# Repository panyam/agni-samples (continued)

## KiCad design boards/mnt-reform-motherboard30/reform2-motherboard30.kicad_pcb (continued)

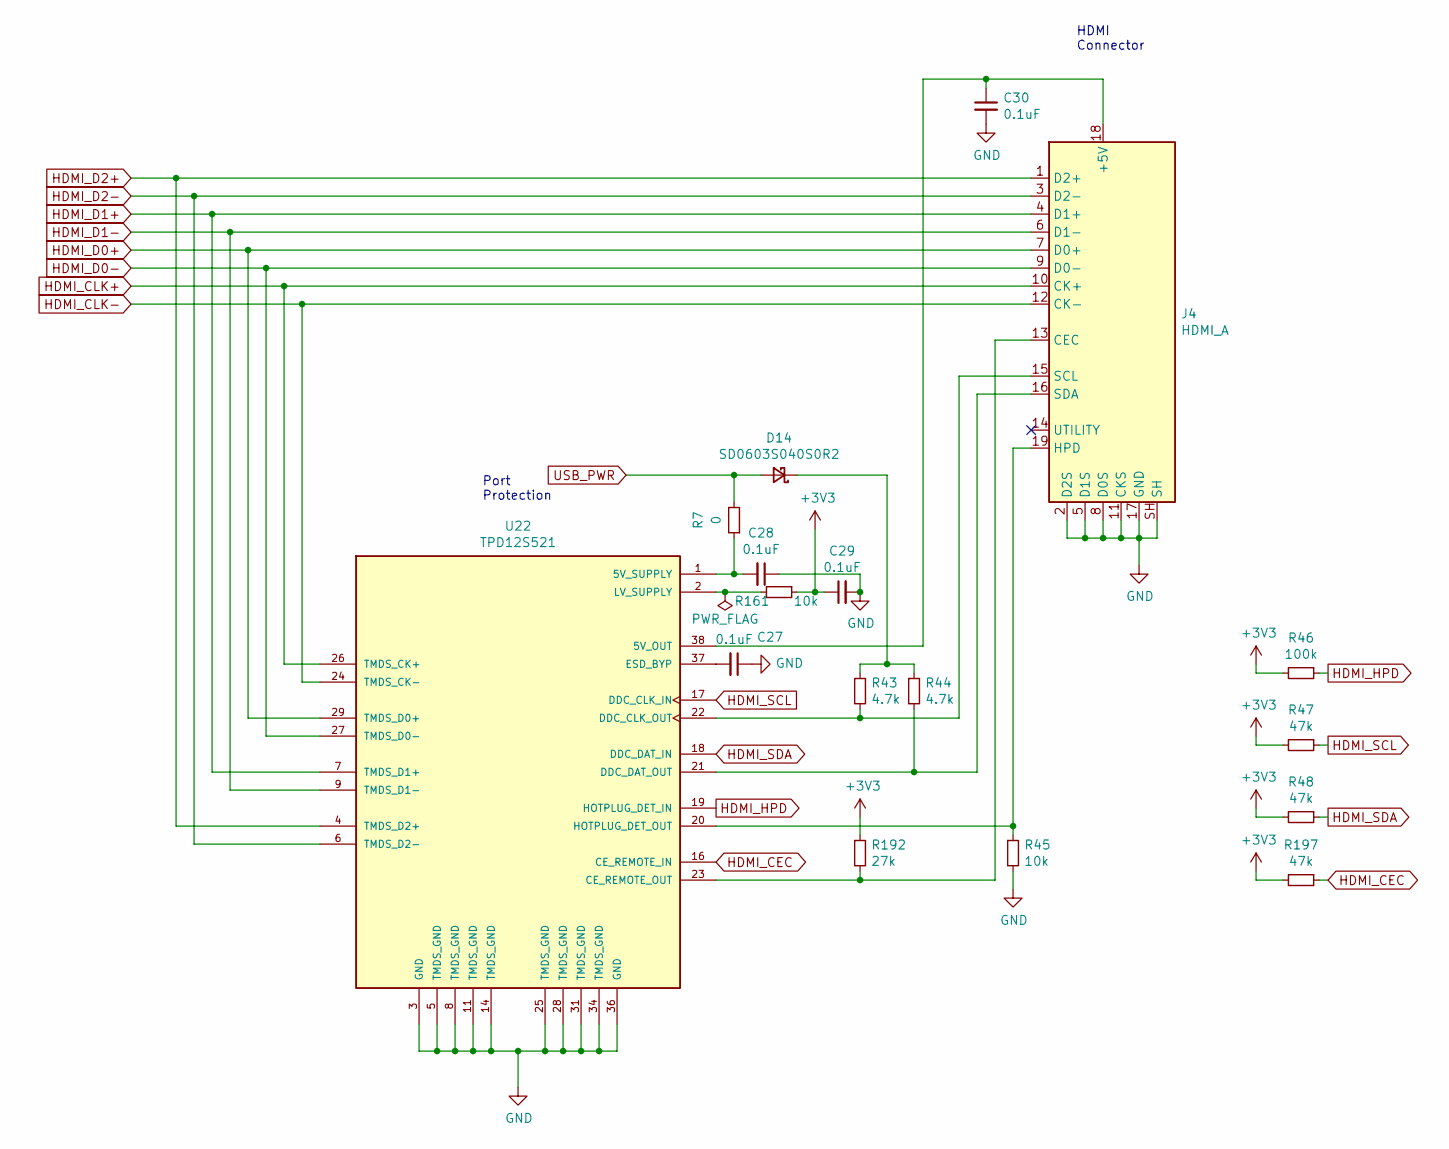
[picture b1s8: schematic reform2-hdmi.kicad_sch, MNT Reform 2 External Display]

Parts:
C27, C28, C29, C30: 0.1uF; C_0603_1608Metric
D14: SD0603S040S0R2; D_0603_1608Metric
J4: HDMI_A; HDMI-685119134923
R7: 0; R_0603_1608Metric
R43, R44: 4.7k; R_0603_1608Metric
R45, R161: 10k; R_0603_1608Metric
R46: 100k; R_0603_1608Metric
R47, R48, R197: 47k; R_0603_1608Metric
R192: 27k; R_0603_1608Metric
U22: TPD12S521; TSSOP50P640X120-38N

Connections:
+3V3: C29.1, R46.2, R47.2, R48.2, R161.1, R192.1, R197.2; also elsewhere on the board
GND: C27.1, C28.1, C29.2, C30.2, J4.2 (D2S), J4.5 (D1S), J4.8 (D0S), J4.11 (CKS), J4.17 (GND), J4.SH, R45.2, U22.3 (GND), U22.5 (TMDS_GND), U22.8 (TMDS_GND), U22.11 (TMDS_GND), U22.14 (TMDS_GND), U22.25 (TMDS_GND), U22.28 (TMDS_GND), U22.31 (TMDS_GND), U22.34 (TMDS_GND), U22.36 (GND); also elsewhere on the board
HDMI_CEC: R197.1, U22.16 (CE_REMOTE_IN); also elsewhere on the board
HDMI_CLK+: J4.10 (CK+), U22.13 (TMDS_CK+), U22.26 (TMDS_CK+); also elsewhere on the board
HDMI_CLK-: J4.12 (CK-), U22.15 (TMDS_CK-), U22.24 (TMDS_CK-); also elsewhere on the board
HDMI_D0+: J4.7 (D0+), U22.10 (TMDS_D0+), U22.29 (TMDS_D0+); also elsewhere on the board
HDMI_D0-: J4.9 (D0-), U22.12 (TMDS_D0-), U22.27 (TMDS_D0-); also elsewhere on the board
HDMI_D1+: J4.4 (D1+), U22.7 (TMDS_D1+), U22.32 (TMDS_D1+); also elsewhere on the board
HDMI_D1-: J4.6 (D1-), U22.9 (TMDS_D1-), U22.30 (TMDS_D1-); also elsewhere on the board
HDMI_D2+: J4.1 (D2+), U22.4 (TMDS_D2+), U22.35 (TMDS_D2+); also elsewhere on the board
HDMI_D2-: J4.3 (D2-), U22.6 (TMDS_D2-), U22.33 (TMDS_D2-); also elsewhere on the board
HDMI_HPD: R46.1, U22.19 (HOTPLUG_DET_IN); also elsewhere on the board
HDMI_SCL: R47.1, U22.17 (DDC_CLK_IN); also elsewhere on the board
HDMI_SDA: R48.1, U22.18 (DDC_DAT_IN); also elsewhere on the board
unnamed: D14.1 (K), R43.1, R44.1
unnamed: C30.1, J4.18 (+5V), U22.38 (5V_OUT)
unnamed: J4.13 (CEC), R192.2, U22.23 (CE_REMOTE_OUT)
unnamed: J4.19 (HPD), R45.1, U22.20 (HOTPLUG_DET_OUT)
unnamed: J4.15 (SCL), R43.2, U22.22 (DDC_CLK_OUT)
unnamed: J4.16 (SDA), R44.2, U22.21 (DDC_DAT_OUT)
unnamed: C28.2, R7.1, U22.1 (5V_SUPPLY)
unnamed: C27.2, U22.37 (ESD_BYP)
unnamed: R161.2, U22.2 (LV_SUPPLY)
USB_PWR: D14.2 (A), R7.2; also elsewhere on the board

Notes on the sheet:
HDMI Connector
Port Protection

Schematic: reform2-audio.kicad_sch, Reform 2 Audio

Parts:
C127, C147: 220uF; C_1210_3225Metric
C139, C151, C170: 4.7uF; C_0603_1608Metric
C141, C162, C163: 1uF; C_0603_1608Metric
C142, C143, C144, C154, C156, C158, C165, C166: 0.1uF; C_0603_1608Metric
C150: 10uF; C_0603_1608Metric
C157, C159: 470nF; C_0603_1608Metric
D10: SP0503BAHT; SOT-143
FB10, FB11, FB16, FB17, FB18, FB19, FB20, FB21: 100@100MHz 3A; L_0603_1608Metric
J7: SJ-43516-SMT
J16: LINE_IN; PinHeader_1x03_P2.00mm_Vertical
J21: Conn_01x04; JST_PH_B4B-PH-K_1x04_P2.00mm_Vertical
L8, L9, L10, L11: 15uH; L_1210_3225Metric
R66, R112: 220; R_0603_1608Metric
R114, R121, R138, R139, R150, R151: 33; R_0603_1608Metric
R135, R136: 4.7k; R_0603_1608Metric
R140: 680; R_0603_1608Metric
R141, R152: 0; R_0603_1608Metric
R142, R143: 47k; R_0603_1608Metric
R144: 220k; R_0603_1608Metric
U3: WM8960; QFN-32-1EP_5x5mm_P0.5mm_EP3.45x3.45mm_ThermalVias

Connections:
+3V3: FB18.1, FB20.1, FB21.1, R135.1, R136.1; also elsewhere on the board
+5V: R152.1; also elsewhere on the board
DAC_BCLK: R114.1; also elsewhere on the board
DAC_DIN: R150.1; also elsewhere on the board
DAC_DOUT: R121.1; also elsewhere on the board
DAC_MCLK: R138.2; also elsewhere on the board
DAC_RXFS: R139.1; also elsewhere on the board
DAC_SCL: R66.1; also elsewhere on the board
DAC_SDA: R112.1; also elsewhere on the board
DAC_TXFS: R151.1; also elsewhere on the board
GND: C139.2, C142.2, C143.2, C144.1, C150.2, C151.2, C154.2, C156.2, C158.2, C165.2, C166.2, C170.2, D10.1 (A), J7.4 (RING2), J16.1, R142.2, R143.2, U3.9 (DGND), U3.20 (SPKGND2), U3.24 (SPKGND1), U3.28 (AGND), U3.33 (GND); also elsewhere on the board
unnamed: FB10.2, L8.1
unnamed: FB11.2, L9.1
unnamed: FB16.2, L10.1
unnamed: FB17.2, L11.1
unnamed: C147.1, D10.4 (K), J7.3 (RING1), R143.1
unnamed: J7.6 (RING_SWITCH), R141.1, R144.2
unnamed: C141.1, D10.2 (K), J7.1 (SLEEVE), R140.2
unnamed: C127.1, D10.3 (K), J7.2 (TIP), R142.1
unnamed: C163.2, J16.2
unnamed: C162.2, J16.3
unnamed: C159.2, C166.1, J21.1, L11.2
unnamed: C159.1, C165.1, J21.2, L10.2
unnamed: C157.2, C158.1, J21.3, L9.2
unnamed: C156.1, C157.1, J21.4, L8.2
unnamed: R150.2, U3.16 (ADCDAT)
unnamed: R139.2, U3.15 (ADCLRC)
unnamed: C142.1, FB21.2, U3.32 (AVDD)
unnamed: R114.2, U3.12 (BCLK)
unnamed: R121.2, U3.14 (DACDAT)
unnamed: R151.2, U3.13 (DACLRC)
unnamed: C143.1, FB20.2, R144.1, U3.10 (DBVDD)
unnamed: C144.2, FB18.2, U3.8 (DCVDD)
unnamed: C127.2, U3.31 (HP_L)
unnamed: C147.2, U3.29 (HP_R)
unnamed: C141.2, U3.4 (LINPUT1)
unnamed: C162.1, U3.3 (LINPUT2)
unnamed: R141.2, U3.2 (LINPUT3)
unnamed: R138.1, U3.11 (MCLK)
unnamed: C170.1, R140.1, U3.1 (MICBIAS)
unnamed: C163.1, U3.6 (RINPUT2)
unnamed: R66.2, R135.2, U3.17 (SCLK)
unnamed: R112.2, R136.2, U3.18 (SDIN)
unnamed: C139.1, C151.1, FB19.2, U3.21 (SPKVDD2), U3.26 (SPKVDD1)
unnamed: FB11.1, U3.23 (SPK_LN)
unnamed: FB10.1, U3.25 (SPK_LP)
unnamed: FB17.1, U3.19 (SPK_RN)
unnamed: FB16.1, U3.22 (SPK_RP)
unnamed: C150.1, C154.1, U3.27 (VMID)
SPK_PWR: FB19.1, R152.2

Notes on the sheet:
value changed in 3.0, thanks chartreuse
CTIA standard TRRS
butterworth filter with 40khz cutoff: speaker ohms = 8 L = 22.5uH C = 0.35uF
Jack Detect
Audio Codec
Speakers: PUI AS01808AO-3-R 8 Ohm 1 W
NOTE: DCVDD could be 1.8v
more bass!
800mA

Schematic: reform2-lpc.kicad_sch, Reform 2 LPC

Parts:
BT1: CR1220; BatteryHolder_Keystone_3000_1x12mm
C7, C49, C50, C140: 0.1uF; C_0603_1608Metric
C46, C47: 10uF; C_0603_1608Metric
C48, C51: 18pF; C_0603_1608Metric; LCSC C107040
J8: USB_C_Receptacle_USB2.0; USB_C_Receptacle_HRO_TYPE-C-31-M-12; LCSC C165948
J18: QWIIC_LPC; JST_SH_SM04B-SRSS-TB_1x04-1MP_P1.00mm_Horizontal
J22: LPC_IO; PinHeader_2x08_P2.54mm_Vertical
J23: KDBSYSCTL; JST_PH_B4B-PH-K_1x04_P2.00mm_Vertical
R41: 0.02; R_0612_1632Metric
R68, R69: 4.7k; R_0603_1608Metric
R70, R72: 33; R_0603_1608Metric
R71, R195: 1.5k; R_0603_1608Metric
R73, R74, R75, R76, R124, R125, R126, R137, R157, R194: 0; R_0603_1608Metric
R128: 10k; R_0603_1608Metric
SW1: SW_DIP_x01; SW_DIP_SPSTx01_Slide_Omron_A6S-110x_W8.9mm_P2.54mm
SW2: SW_Push; UK-B0206-G3.8-250-JZ
TP4: LPCUSB_VBUS; TestPoint_Pad_D1.0mm; not fitted
U5: PCF8523T; SOIC-8_3.9x4.9mm_P1.27mm
U6: INA233; VSSOP-10_3x3mm_P0.5mm
U18: LPC11U24FBD48-301; LQFP-48_7x7mm_P0.5mm
Y2: 12MHz; Crystal_SMD_Abracon_ABM8G-4Pin_3.2x2.5mm
Y4: 32.768 kHz; Crystal_SMD_3215-2Pin_3.2x1.5mm

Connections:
1V2_PWR_EN: U18.2 (PIO1_19); also elsewhere on the board
3V3_PWR_EN: U18.48 (PIO1_16); also elsewhere on the board
5V_PWR_EN: U18.43 (PIO1_15); also elsewhere on the board
/Reform 2 Power/Reform 2 LPC/LPCUD_N: R72.2, U18.19 (USB_DM)
/Reform 2 Power/Reform 2 LPC/LPCUD_P: R70.2, U18.20 (USB_DP)
/Reform 2 Power/Reform 2 LPC/LPCUSB_VBUS: J8.A4 (VBUS), J8.A9 (VBUS), J8.B4 (VBUS), J8.B9 (VBUS), TP4.1
/Reform 2 Power/Reform 2 LPC/LPC_AD5: J22.7, U18.40 (PIO0_16)
/Reform 2 Power/Reform 2 LPC/LPC_AD7: J22.10, U18.42 (PIO0_23)
/Reform 2 Power/Reform 2 LPC/LPC_MISO0: R124.1, U18.27 (PIO0_8)
/Reform 2 Power/Reform 2 LPC/LPC_MISO1a: J22.2, U18.30 (PIO0_22)
/Reform 2 Power/Reform 2 LPC/LPC_MISO1b: R74.2, U18.26 (PIO1_21)
/Reform 2 Power/Reform 2 LPC/LPC_MOSI0: R125.1, U18.28 (PIO0_9)
/Reform 2 Power/Reform 2 LPC/LPC_MOSI1a: J22.14, U18.17 (PIO0_21)
/Reform 2 Power/Reform 2 LPC/LPC_MOSI1b: R75.2, U18.38 (PIO1_22)
/Reform 2 Power/Reform 2 LPC/LPC_RXDc: J23.3, U18.11 (PIO1_26)
/Reform 2 Power/Reform 2 LPC/LPC_SCK0a: R126.1, U18.29 (PIO0_10)
/Reform 2 Power/Reform 2 LPC/LPC_SCK0b: J22.1, U18.31 (PIO1_29)
/Reform 2 Power/Reform 2 LPC/LPC_SCK1b: R73.2, U18.13 (PIO1_20)
/Reform 2 Power/Reform 2 LPC/LPC_SCLKa: J22.9, U18.45 (PIO0_17)
/Reform 2 Power/Reform 2 LPC/LPC_SCLKc: R194.2, U18.24 (PIO1_28)
/Reform 2 Power/Reform 2 LPC/LPC_SSEL0: R157.1, U18.10 (PIO0_2)
/Reform 2 Power/Reform 2 LPC/LPC_SSEL1: R76.2, U18.18 (PIO1_23)
/Reform 2 Power/Reform 2 LPC/LPC_SWDIO: J22.8, U18.39 (PIO0_15)
/Reform 2 Power/Reform 2 LPC/LPC_TDI: J22.4, U18.32 (PIO0_11)
/Reform 2 Power/Reform 2 LPC/LPC_TDO: J22.6, U18.34 (PIO0_13)
/Reform 2 Power/Reform 2 LPC/LPC_TMS: J22.3, U18.33 (PIO0_12)
/Reform 2 Power/Reform 2 LPC/LPC_TXDc: J23.2, U18.12 (PIO1_27)
/Reform 2 Power/Reform 2 LPC/LPC_UFTOGG: SW1.2, U18.4 (PIO0_1)
/Reform 2 Power/Reform 2 LPC/LPC_UVBUS: R195.2, U18.14 (PIO0_3)
/Reform 2 Power/Reform 2 LPC/LPC_~TRST: J22.5, U18.35 (PIO0_14)
/Reform 2 Power/Reform 2 LPC/LPC_~USBCON: J22.13, U18.22 (PIO0_6)
AUX_PWR_EN: U18.23 (PIO0_7)
BAT1FUSED: R41.1, U6.10 (Vin+); also elsewhere on the board
BMON_CS: R76.1; also elsewhere on the board
BMON_SCK: R73.1; also elsewhere on the board
BMON_SDI: R75.1; also elsewhere on the board
BMON_SDO: R74.1, R128.1; also elsewhere on the board
CHGBAT: R41.2, U6.8 (Vbus), U6.9 (Vin-); also elsewhere on the board
CHG_RNG: U18.1 (PIO1_25); also elsewhere on the board
DAC_SCL: U5.6 (SCL); also elsewhere on the board
DAC_SDA: U5.5 (SDA); also elsewhere on the board
GND: BT1.2 (-), C7.2, C46.2, C47.2, C48.2, C49.2, C50.2, C51.2, C140.1, J8.A1 (GND), J8.A12 (GND), J8.B1 (GND), J8.B12 (GND), J8.S1 (SHIELD), J18.1, J22.16, J23.4, SW1.1, SW2.1, U5.4 (VSS), U6.1 (A1), U6.2 (A0), U6.7 (GND), U18.5 (VSS), U18.41 (VSS), Y2.2, Y2.4; also elsewhere on the board
IMX_RESETn: R194.1; also elsewhere on the board
IMX_RTC_IRQ: R137.1; also elsewhere on the board
IMX_WAKE: U18.21 (PIO1_24); also elsewhere on the board
INA_SCL: J18.4, R69.2, U6.5 (SCL), U18.15 (PIO0_4); also elsewhere on the board
INA_SDA: J18.3, R68.2, U6.4 (SDA), U18.16 (PIO0_5); also elsewhere on the board
LPC_MISO: R124.2; also elsewhere on the board
LPC_MOSI: R125.2; also elsewhere on the board
LPC_RXDa: J22.12, U18.46 (PIO0_18); also elsewhere on the board
LPC_SCK: R126.2; also elsewhere on the board
LPC_SS0: R157.2; also elsewhere on the board
LPC_TXDa: J22.11, U18.47 (PIO0_19); also elsewhere on the board
LPC_UART2_RX: U18.37 (PIO1_14); also elsewhere on the board
LPC_UART2_TX: U18.36 (PIO1_13); also elsewhere on the board
LPC_VCC: C7.1, C46.1, C47.1, C49.1, C50.1, C140.2, J18.2, J22.15, J23.1, R68.1, R69.1, R71.1, R128.2, R195.1, U5.8 (VDD), U6.6 (VS), U18.8 (VDD), U18.44 (VDD); also elsewhere on the board
LPC_~RESET: SW2.2, U18.3 (PIO0_0)
unnamed: BT1.1 (+), U5.3 (VBAT)
unnamed: J8.A6 (D+), J8.B6 (D+), R70.1, R71.2
unnamed: J8.A7 (D-), J8.B7 (D-), R72.1
unnamed: U5.1 (OSCI), Y4.1
unnamed: U5.2 (OSCO), Y4.2
unnamed: R137.2, U5.7 (~INT1/CLKOUT)
unnamed: C51.1, U18.6 (XTALIN), Y2.3
unnamed: C48.1, U18.7 (XTALOUT), Y2.1
PCIE1_PWR_EN: U18.9 (PIO0_20); also elsewhere on the board
USB_PWR_EN: U18.25 (PIO1_31)

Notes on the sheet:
LPC Flashing Port
no longer used
System Controller
Expansion Port
I2C lines pulled up by SYS 3v3 power near DAC
Power Switches
Keyboard System Control Port (SYSCTL)
Powered by coin cell when batteries removed
Powered by main batteries in standby
LPC Qwiic I2C Interface
I2C ADDR 1000_000
Voltage / Current Monitor
Realtime Clock

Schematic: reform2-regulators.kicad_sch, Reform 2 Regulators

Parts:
C3: 0.33uF; C_0603_1608Metric
C16, C19, C148, C172: 10uF; C_0805_2012Metric
C17, C18, C149, C171: 470nF; C_0603_1608Metric; LCSC C1589
C33, C35, C167, C188: 4.7uF; C_0603_1608Metric
C34, C37: 10uF; C_0603_1608Metric
C36, C38: 6.8pF; C_0603_1608Metric
C82: 2.2uF; C_0603_1608Metric
C93, C94, C95, C96, C97, C173, C174, C175, C176, C177: 22uF; C_0603_1608Metric; LCSC C140782
C121: 47uF; C_0603_1608Metric
C128, C178: 0.1uF; C_0402_1005Metric; LCSC C1589
C145, C179: 10pF; C_0402_1005Metric; LCSC C1589
C146, C180: 1uF; C_0402_1005Metric; LCSC C1589
D3: SBR0560S1; D_SOD-123
D11: LED3V; LED_0603_1608Metric
D12: LED5V; LED_0603_1608Metric
D15, D16: BZX584C3V3-G3-08; D_SOD-523
L3: 2.7uH; L_Coilcraft_XAL6060-XXX
L4: 2.2uH; L_Coilcraft_XAL6060-XXX
L5: 10uH; L_1210_3225Metric
L6, L7: 2.2uH; L_1210_3225Metric
R33, R164: 4.7k; R_0603_1608Metric
R90, R100: 100k; R_0402_1005Metric; LCSC C60490
R91, R104: 4.99k; R_0402_1005Metric; LCSC C60490
R92, R105: 10k; R_0402_1005Metric
R93: 24.9k; R_0402_1005Metric; LCSC C163466
R96, R107: 100k; R_0402_1005Metric; LCSC C60491
R98, R185, R186: 0; R_0603_1608Metric
R106: 43.2k; R_0402_1005Metric; LCSC C163466
R178, R179, R181: 100k; R_0603_1608Metric
R180: 150k; R_0603_1608Metric
R188, R189: 10k; R_0603_1608Metric
U7, U9: LM62460; CONV_LM61495QRPHRQ1
U13, U19: TLV62568DBV; SOT-23-5
U14: LMR16006YQ3; TSOT-23-6
U17: TPS70918DBVR; SOT-23-5

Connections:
1V2_PWR_EN: R185.1; also elsewhere on the board
3V3_PWR_EN: D16.1 (K), R105.1, U9.13 (EN); also elsewhere on the board
5V_PWR_EN: D15.1 (K), R92.1, U7.13 (EN); also elsewhere on the board
30V_GATE: C16.1, C17.1, C18.1, C19.1, C82.2, C148.1, C149.1, C171.1, C172.1, U7.2 (VIN2), U7.14 (VIN1), U9.2 (VIN2), U9.14 (VIN1), U14.5 (VIN); also elsewhere on the board
+1V2: C36.1, C37.1, L6.2, R178.1; also elsewhere on the board
+1V5: C34.1, C38.1, L7.2, R180.1; also elsewhere on the board
+1V8: C188.1, U17.5 (OUT); also elsewhere on the board
+3V3: C173.1, C174.1, C175.1, C176.1, C177.1, D11.2 (A), L4.2, R98.2, R100.1, R104.1, R107.2, U9.5 (BIAS); also elsewhere on the board
+5V: C33.1, C35.1, C93.1, C94.1, C95.1, C96.1, C97.1, D12.2 (A), L3.2, R90.1, R91.1, R96.2, U7.5 (BIAS), U13.4 (VIN), U19.4 (VIN); also elsewhere on the board
GND: C16.2, C17.2, C18.2, C19.2, C33.2, C34.2, C35.2, C37.2, C82.1, C93.2, C94.2, C95.2, C96.2, C97.2, C121.1, C146.1, C148.2, C149.2, C167.2, C171.2, C172.2, C173.2, C174.2, C175.2, C176.2, C177.2, C180.1, C188.2, D3.2 (A), D15.2 (A), D16.2 (A), R33.1, R92.2, R93.2, R105.2, R106.2, R164.1, R179.2, R181.2, R188.2, R189.2, U7.1 (PGND2), U7.8 (AGND), U7.12 (SYNC/MODE), U7.15 (PGND1), U9.1 (PGND2), U9.8 (AGND), U9.12 (SYNC/MODE), U9.15 (PGND1), U13.2 (GND), U14.2 (GND), U17.2 (GND), U19.2 (GND); also elsewhere on the board
LPC_VCC: C121.2, L5.2, U14.3 (FB); also elsewhere on the board
unnamed: C145.2, R91.2
unnamed: C179.2, R104.2
unnamed: C3.1, D3.1 (K), L5.1, U14.6 (SW)
unnamed: D11.1 (K), R33.2
unnamed: D12.1 (K), R164.2
unnamed: C128.1, U7.3 (RBOOT), U7.4 (CBOOT)
unnamed: C145.1, R90.2, R93.1, U7.7 (FB)
unnamed: R96.1, U7.10 (RESET)
unnamed: C146.2, U7.6 (VCC), U7.9 (RT), U7.11 (SPSP)
unnamed: C128.2, L3.1, U7.16 (SW)
unnamed: C178.1, U9.3 (RBOOT), U9.4 (CBOOT)
unnamed: C179.1, R100.2, R106.1, U9.7 (FB)
unnamed: R107.1, U9.10 (RESET)
unnamed: C180.2, U9.6 (VCC), U9.9 (RT), U9.11 (SPSP)
unnamed: C178.2, L4.1, U9.16 (SW)
unnamed: R185.2, R188.1, U13.1 (EN)
unnamed: C36.2, R178.2, R179.1, U13.5 (FB)
unnamed: L6.1, U13.3 (SW)
unnamed: C3.2, U14.1 (BOOST)
unnamed: C167.1, R98.1, U17.1 (IN), U17.3 (EN)
unnamed: R186.2, R189.1, U19.1 (EN)
unnamed: C38.2, R180.2, R181.1, U19.5 (FB)
unnamed: L7.1, U19.3 (SW)
PCIE1_PWR_EN: R186.1; also elsewhere on the board

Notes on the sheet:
Standby always-on 3V3 power rail
Note: 10A possible with LM61495-Q1
Rfbt
Cff
Power LEDs
Rff
Rfbb
Up to 1A (peak) 375mA normal from mPCIe
Up to 70mA consumed by DSI bridge
10A
Up to 780mA (!) consumed by USB hub
MAX 36V
VCCIO supply for DSI + SD
Up to 40mA consumed by DSI bridge and SD card level shifter
Main system power converters, enabled by LPC

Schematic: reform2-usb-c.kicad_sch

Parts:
C66, C67: 330pF; C_0603_1608Metric
C68, C80, C184: 4.7uF; C_0603_1608Metric
C74, C78, C187: 10uF; C_0603_1608Metric
C92: 1uF; C_0603_1608Metric
C129: 2.2uF; C_0603_1608Metric
C130: 0.33uF; C_0603_1608Metric
C185, C186: 10nF; C_0603_1608Metric
D1: SP0503BAHT; SOT-143
D5: SBR0560S1; D_SOD-123
D13: P4SMA24CA-E3/61; D_SMA
J1: POWER; JST_PH_B2B-PH-K_1x02_P2.00mm_Vertical
J12: USB_C_Receptacle_USB2.0; USB_C_Receptacle_HRO_TYPE-C-31-M-12; LCSC C165948
L12: 10uH; L_1210_3225Metric
R2, R57, R83, R85, R120: 0; R_0603_1608Metric
R55, R59, R63, R84: 10k; R_0603_1608Metric
R87: 198k; R_0603_1608Metric
R97: 2.26k; R_0603_1608Metric
R108: 9.31k; R_0603_1608Metric
R109, R118: 191k; R_0603_1608Metric
R116: 162k; R_0603_1608Metric
R117: 38.3k; R_0603_1608Metric
R119: 9.53k; R_0603_1608Metric
SW4: SW_DIP_x06; SW_DIP_SPSTx06_Slide_KingTek_DSHP06TJ_W5.25mm_P1.27mm_JPin
TP2, TP3, TP5, TP6: TestPoint; TestPoint_Pad_D1.0mm; not fitted
TP7: UUART_SUSPEND; TestPoint_Pad_D1.0mm; not fitted
TP8: UUART_WAKEUP; TestPoint_Pad_D1.0mm; not fitted
TP9: UUART_nPOWER; TestPoint_Pad_D1.0mm; not fitted
U12: LMR16006YQ3; TSOT-23-6
U16: CY7C65215-32LTXI; QFN-32-1EP_5x5mm_P0.5mm_EP3.45x3.45mm
U24: TPS25730DREFR; Mouser Part Number 595-TPS25730DREFR

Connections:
/Reform 2 Power/Reform 2 USB-C/TPS_ADCIN1: R87.2, R97.1, U24.2 (ADCIN1)
/Reform 2 Power/Reform 2 USB-C/TPS_ADCIN2: R108.2, R109.1, U24.3 (ADCIN2)
/Reform 2 Power/Reform 2 USB-C/TPS_ADCIN3: R116.2, R117.1, U24.5 (ADCIN3)
/Reform 2 Power/Reform 2 USB-C/TPS_ADCIN4: R118.2, R119.1, U24.7 (ADCIN4)
/Reform 2 Power/Reform 2 USB-C/TPS_CAP_MIS: TP2.1, U24.6 (CAP_MIS)
/Reform 2 Power/Reform 2 USB-C/TPS_DBG_ACC: TP5.1, U24.10 (DBG_ACC)
/Reform 2 Power/Reform 2 USB-C/TPS_DRAIN: U24.15 (DRAIN_1), U24.30 (DRAIN_2), U24.40 (DRAIN_3)
/Reform 2 Power/Reform 2 USB-C/TPS_LDO_1V5: C68.1, U24.4 (LDO_1V5)
/Reform 2 Power/Reform 2 USB-C/TPS_LDO_3V3: C74.1, R84.1, R87.1, R108.1, R116.1, R118.1, U24.1 (LDO_3V3)
/Reform 2 Power/Reform 2 USB-C/TPS_NSINK_EN: TP6.1, U24.19 (~SINK_EN)
/Reform 2 Power/Reform 2 USB-C/TPS_PLUG_EVENT: TP3.1, U24.37 (PLUG_EVENT)
/Reform 2 Power/Reform 2 USB-C/USB_UART_3V3: C80.1, C187.2, L12.2, R120.2, U12.3 (FB), U16.1 (VDDD), U16.23 (VDDD)
GND: C66.1, C67.1, C68.2, C74.2, C78.2, C80.2, C92.2, C129.1, C184.2, C185.2, C186.2, C187.1, D1.1 (A), D5.2 (A), D13.2 (A), J1.2, J12.A1 (GND), J12.A12 (GND), J12.B1 (GND), J12.B12 (GND), J12.S1 (SHIELD), R55.2, R59.2, R63.2, R97.2, R109.2, R117.2, R119.2, U12.2 (GND), U16.4 (VSSD), U16.17 (VSSD), U16.20 (VSSD), U16.24 (VSSA), U24.11 (GND_1), U24.12 (GND_2), U24.14 (GND_3), U24.16 (GND_4), U24.17 (GND_5), U24.31 (GND_6), U24.34 (GND_7), U24.35 (GND_8), U24.39 (GND_9), U24.44 (GND_10); also elsewhere on the board
IMX_UART1_RX: SW4.2; also elsewhere on the board
IMX_UART1_TX: SW4.1; also elsewhere on the board
IMX_UART2_RX: SW4.4; also elsewhere on the board
IMX_UART2_TX: SW4.3; also elsewhere on the board
INA_SCL: R83.1; also elsewhere on the board
INA_SDA: R57.1; also elsewhere on the board
LPC_RXDa: SW4.6; also elsewhere on the board
LPC_TXDa: SW4.5; also elsewhere on the board
LPC_VCC: R85.1; also elsewhere on the board
unnamed: C130.1, D5.1 (K), L12.1, U12.6 (SW)
unnamed: C66.2, J12.A5 (CC1), U24.28 (CC1)
unnamed: C67.2, J12.B5 (CC2), U24.29 (CC2)
unnamed: C130.2, U12.1 (BOOST)
unnamed: C129.2, R2.2, U12.5 (VIN)
unnamed: TP9.1, U16.31 (GPIO_6)
unnamed: SW4.10, SW4.12, U16.2 (SCB0_0/GPIO_8)
unnamed: SW4.9, SW4.11, U16.30 (SCB0_4/GPIO_5)
unnamed: SW4.8, U16.5 (SCB1_0/GPIO_10)
unnamed: SW4.7, U16.6 (SCB1_1/GPIO_11)
unnamed: TP7.1, U16.11 (SUSPEND)
unnamed: R120.1, U16.19 (VBUS)
unnamed: TP8.1, U16.12 (WAKEUP)
unnamed: R83.2, U24.9 (I2CT_SCL)
unnamed: R57.2, U24.8 (I2CT_SDA)
unnamed: R55.1, U24.26 (RESERVED_1)
unnamed: R59.1, U24.27 (RESERVED_2)
unnamed: R63.1, U24.36 (RESERVED_3)
unnamed: C78.1, R85.2, U24.38 (VIN_3V3)
unnamed: R84.2, U24.18 (~FAULT_IN)
VBUS_PD: C184.1, C185.1, C186.1, D13.1 (K), J12.A4 (VBUS), J12.A9 (VBUS), J12.B4 (VBUS), J12.B9 (VBUS), U24.23 (VBUS_IN_1), U24.24 (VBUS_IN_2), U24.25 (VBUS_IN_3), U24.32 (VBUS_1), U24.33 (VBUS_2), U24.42 (VBUS_IN_4), U24.43 (VBUS_3)
VIN: J1.1, R2.1, U24.20 (PPHV_1), U24.21 (PPHV_2), U24.22 (PPHV_3), U24.41 (PPHV_4); also elsewhere on the board
XU+: D1.3 (K), J12.A6 (D+), J12.B6 (D+), U16.14 (USBDP)
XU-: D1.2 (K), J12.A7 (D-), J12.B7 (D-), U16.15 (USBDM)

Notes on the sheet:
thermal pad only
Generic Power Header (Skips USB-C PD) ~5V-24V MAX
Working: 20.5V Breakdown: 22.8V Clamping: 33.2V
UART-USB power rail only active when usb-c or direct VIN supply is connected

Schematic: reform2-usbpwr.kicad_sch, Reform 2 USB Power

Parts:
C9, C11, C12, C13, C14, C15, C20, C21, C43, C88, C90: 0.1uF; C_0603_1608Metric
C73, C87, C89: 1uF; C_0603_1608Metric
C91, C92: 10uF; C_0603_1608Metric
F3: 0157004.DR; fuse_smf
FB1, FB2: 220@100MHz 1.4A; L_0603_1608Metric

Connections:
+1V2: FB2.1; also elsewhere on the board
+3V3: FB1.1; also elsewhere on the board
+5V: F3.1; also elsewhere on the board
GND: C9.2, C11.2, C12.2, C13.2, C14.2, C15.2, C20.2, C21.2, C43.2, C73.2, C87.2, C88.2, C89.2, C90.2, C91.2, C92.2; also elsewhere on the board
USB_PWR: F3.2; also elsewhere on the board

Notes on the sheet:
Up to 780mA load!
1V1 is slightly overdriven by 1.2V. Datasheet says 1.26V max.

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
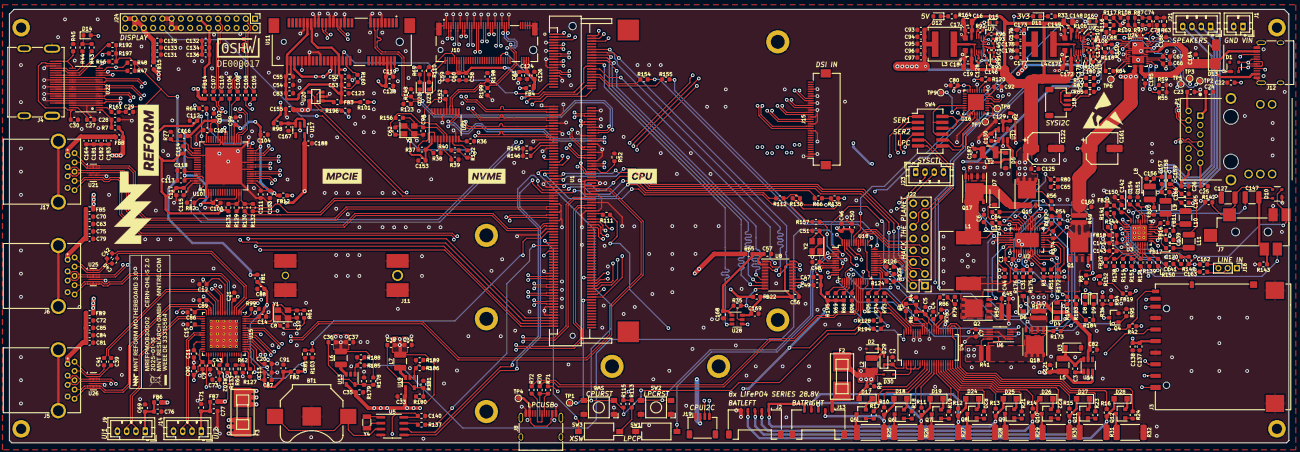
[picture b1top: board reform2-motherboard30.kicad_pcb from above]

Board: 6 copper layers, 276.0 x 93.5 mm, 529 parts (0 on the bottom side), 463 nets.

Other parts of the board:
C86: 1uF; C_0603_1608Metric

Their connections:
GND: C86.2; also elsewhere on the board
